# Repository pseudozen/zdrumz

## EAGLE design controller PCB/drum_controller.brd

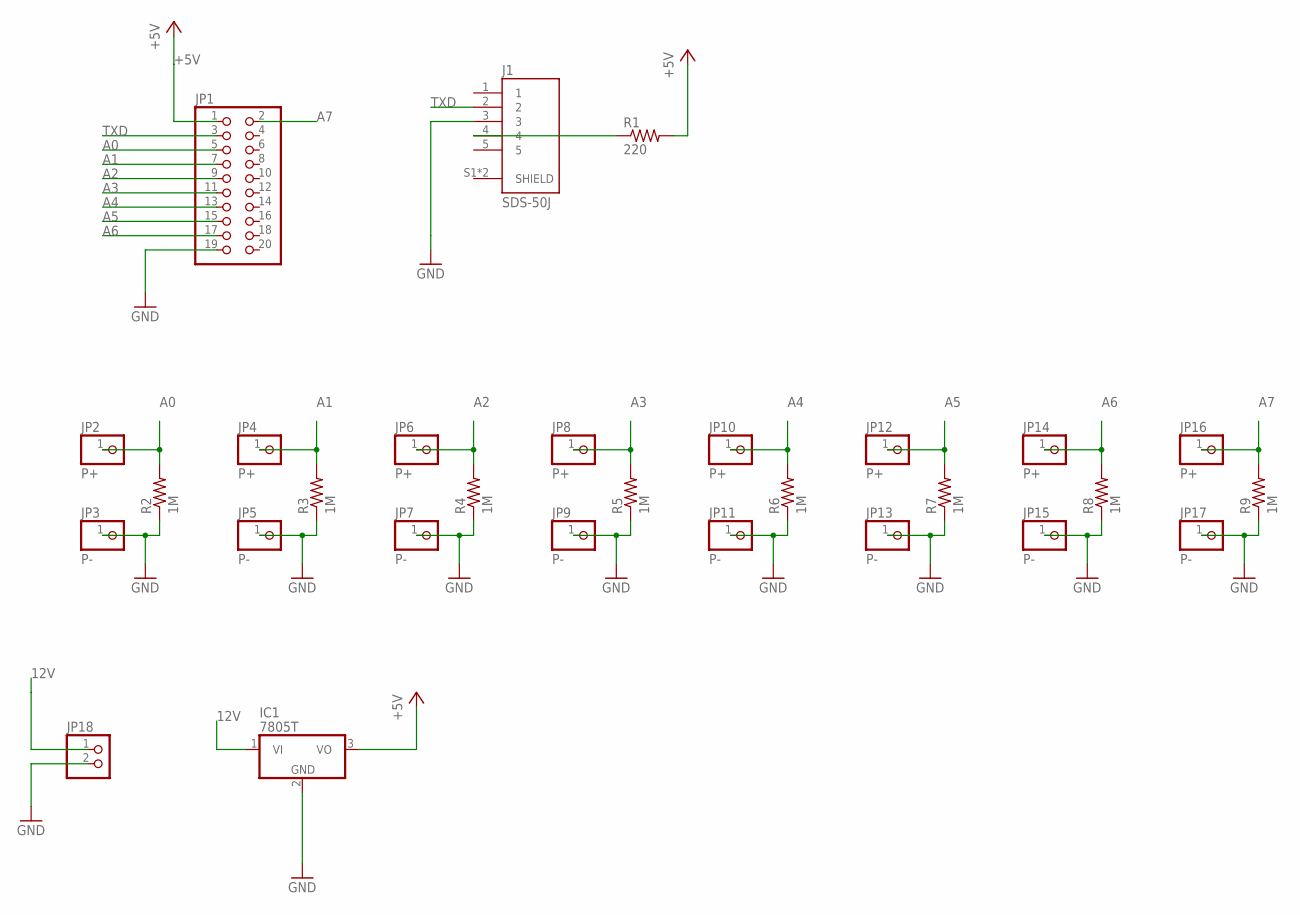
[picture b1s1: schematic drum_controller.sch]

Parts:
IC1: 7805T; TO220H
J1: SDS-50J; CUI_SDS-50J
JP1: PINHD-2X10; 2X10
JP2, JP4, JP6, JP8, JP10, JP12, JP14, JP16: P+; 1X01
JP3, JP5, JP7, JP9, JP11, JP13, JP15, JP17: P-; 1X01
JP18: PINHD-1X2; 1X02
R1: 220; P0817/22
R2, R3, R4, R5, R6, R7, R8, R9: 1M; P0817/22

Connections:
12V: IC1.1 (VI), JP18.1
+5V: IC1.3 (VO), JP1.1, R1.2
A0: JP1.5, JP2.1, R2.2
A1: JP1.7, JP4.1, R3.2
A2: JP1.9, JP6.1, R4.2
A3: JP1.11, JP8.1, R5.2
A4: JP1.13, JP10.1, R6.2
A5: JP1.15, JP12.1, R7.2
A6: JP1.17, JP14.1, R8.2
A7: JP1.2, JP16.1, R9.2
GND: IC1.2 (GND), J1.3, JP1.19, JP3.1, JP5.1, JP7.1, JP9.1, JP11.1, JP13.1, JP15.1, JP17.1, JP18.2, R2.1, R3.1, R4.1, R5.1, R6.1, R7.1, R8.1, R9.1
unnamed: J1.4, R1.1
TXD: J1.2, JP1.3

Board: 2 copper layers, 29 parts (0 on the bottom side), 13 nets, no tracks yet.

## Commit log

2018-08-05 initial board and schematic files
2018-08-05 connected LED anode to +5V
2018-08-05 added all 8 piezos to schematic, board not layed out yet
2018-08-05 resized PCB to match Hammond 1898 enclosure (notches need to be completed)
2018-08-05 added proper MIDI jack from external library; added lower enclosure notch (will add matching notch with Zoe)
2018-12-06 added 3D cad models and ESP32, and almost completed the board layout and routing
